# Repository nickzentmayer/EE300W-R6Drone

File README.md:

# EE300W-R6Drone
Repository containing all code and CAD design files for EE300W project SP26

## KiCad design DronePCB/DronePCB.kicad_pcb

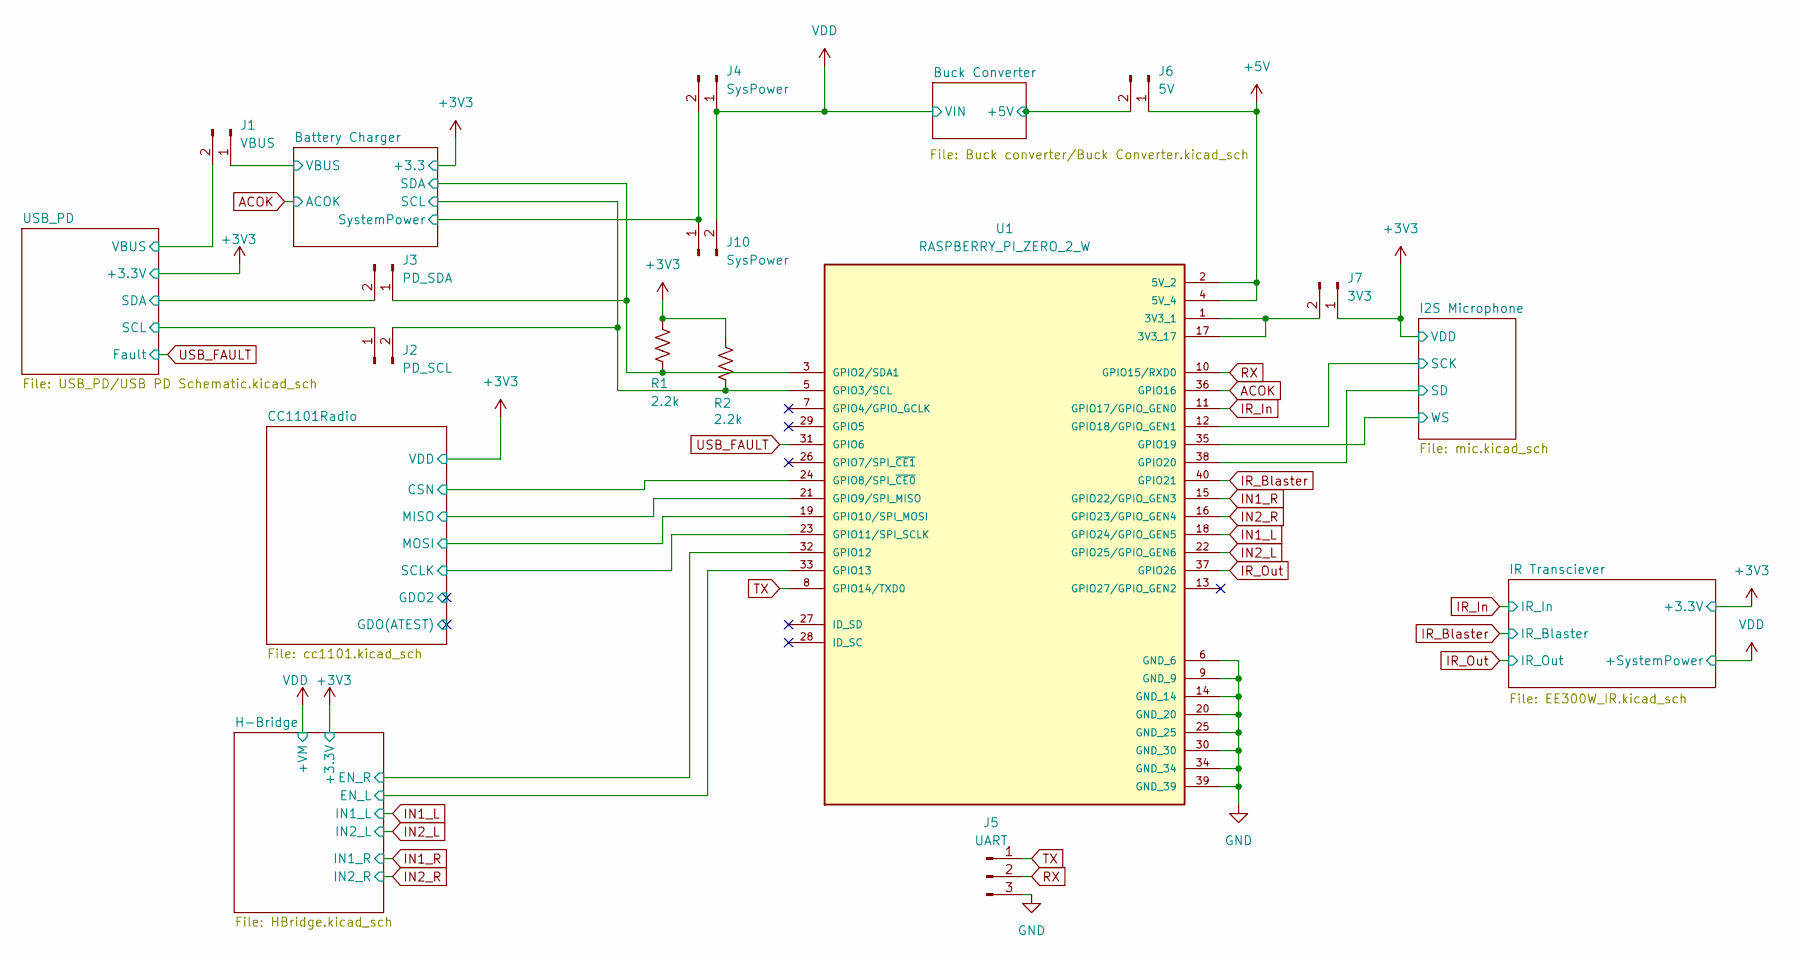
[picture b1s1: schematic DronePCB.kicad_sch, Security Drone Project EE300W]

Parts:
J1: VBUS; PinHeader_1x02_P2.54mm_Vertical
J2: PD_SCL; PinHeader_1x02_P2.54mm_Vertical
J3: PD_SDA; PinHeader_1x02_P2.54mm_Vertical
J4, J10: SysPower; PinHeader_1x02_P2.54mm_Vertical
J5: UART; PinHeader_1x03_P2.54mm_Vertical
J6: 5V; PinHeader_1x02_P2.54mm_Vertical
J7: 3V3; PinHeader_1x02_P2.54mm_Vertical
R1, R2: 2.2k; R_0603_1608Metric
U1: RASPBERRY_PI_ZERO_2_W; MODULE_RASPBERRY_PI_ZERO_2_W; PARTREV April 2024

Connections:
+3V3: J7.1, R1.1, R2.1; also elsewhere on the board
+5V: J6.1, U1.2 (5V_2), U1.4 (5V_4)
/Battery Charger/SCL: J2.2, R2.2, U1.5 (GPIO3/SCL); also elsewhere on the board
/Battery Charger/SDA: J3.1, R1.2, U1.3 (GPIO2/SDA1); also elsewhere on the board
/Battery Charger/SystemPower: J4.2, J10.1; also elsewhere on the board
/Battery Charger/VBUS: J1.1; also elsewhere on the board
/Buck Converter/+5V: J6.2; also elsewhere on the board
/CC1101Radio/CSN: U1.24 (GPIO8/SPI_~CE0); also elsewhere on the board
/CC1101Radio/MISO: U1.21 (GPIO9/SPI_MISO); also elsewhere on the board
/CC1101Radio/MOSI: U1.19 (GPIO10/SPI_MOSI); also elsewhere on the board
/CC1101Radio/SCLK: U1.23 (GPIO11/SPI_SCLK); also elsewhere on the board
/H-Bridge/EN_L: U1.33 (GPIO13); also elsewhere on the board
/H-Bridge/EN_R: U1.32 (GPIO12); also elsewhere on the board
/I2S Microphone/SCK: U1.12 (GPIO18/GPIO_GEN1); also elsewhere on the board
/I2S Microphone/SD: U1.38 (GPIO20); also elsewhere on the board
/I2S Microphone/WS: U1.35 (GPIO19); also elsewhere on the board
/USB_PD/SCL: J2.1; also elsewhere on the board
/USB_PD/SDA: J3.2; also elsewhere on the board
/USB_PD/VBUS: J1.2; also elsewhere on the board
ACOK: U1.36 (GPIO16); also elsewhere on the board
GND: J5.3, U1.6 (GND_6), U1.9 (GND_9), U1.14 (GND_14), U1.20 (GND_20), U1.25 (GND_25), U1.30 (GND_30), U1.34 (GND_34), U1.39 (GND_39); also elsewhere on the board
IN1_L: U1.18 (GPIO24/GPIO_GEN5); also elsewhere on the board
IN1_R: U1.15 (GPIO22/GPIO_GEN3); also elsewhere on the board
IN2_L: U1.22 (GPIO25/GPIO_GEN6); also elsewhere on the board
IN2_R: U1.16 (GPIO23/GPIO_GEN4); also elsewhere on the board
IR_Blaster: U1.40 (GPIO21); also elsewhere on the board
IR_In: U1.11 (GPIO17/GPIO_GEN0); also elsewhere on the board
IR_Out: U1.37 (GPIO26); also elsewhere on the board
unnamed: J7.2, U1.1 (3V3_1), U1.17 (3V3_17)
RX: J5.2, U1.10 (GPIO15/RXD0)
TX: J5.1, U1.8 (GPIO14/TXD0)
USB_FAULT: U1.31 (GPIO6); also elsewhere on the board
VDD: J4.1, J10.2; also elsewhere on the board

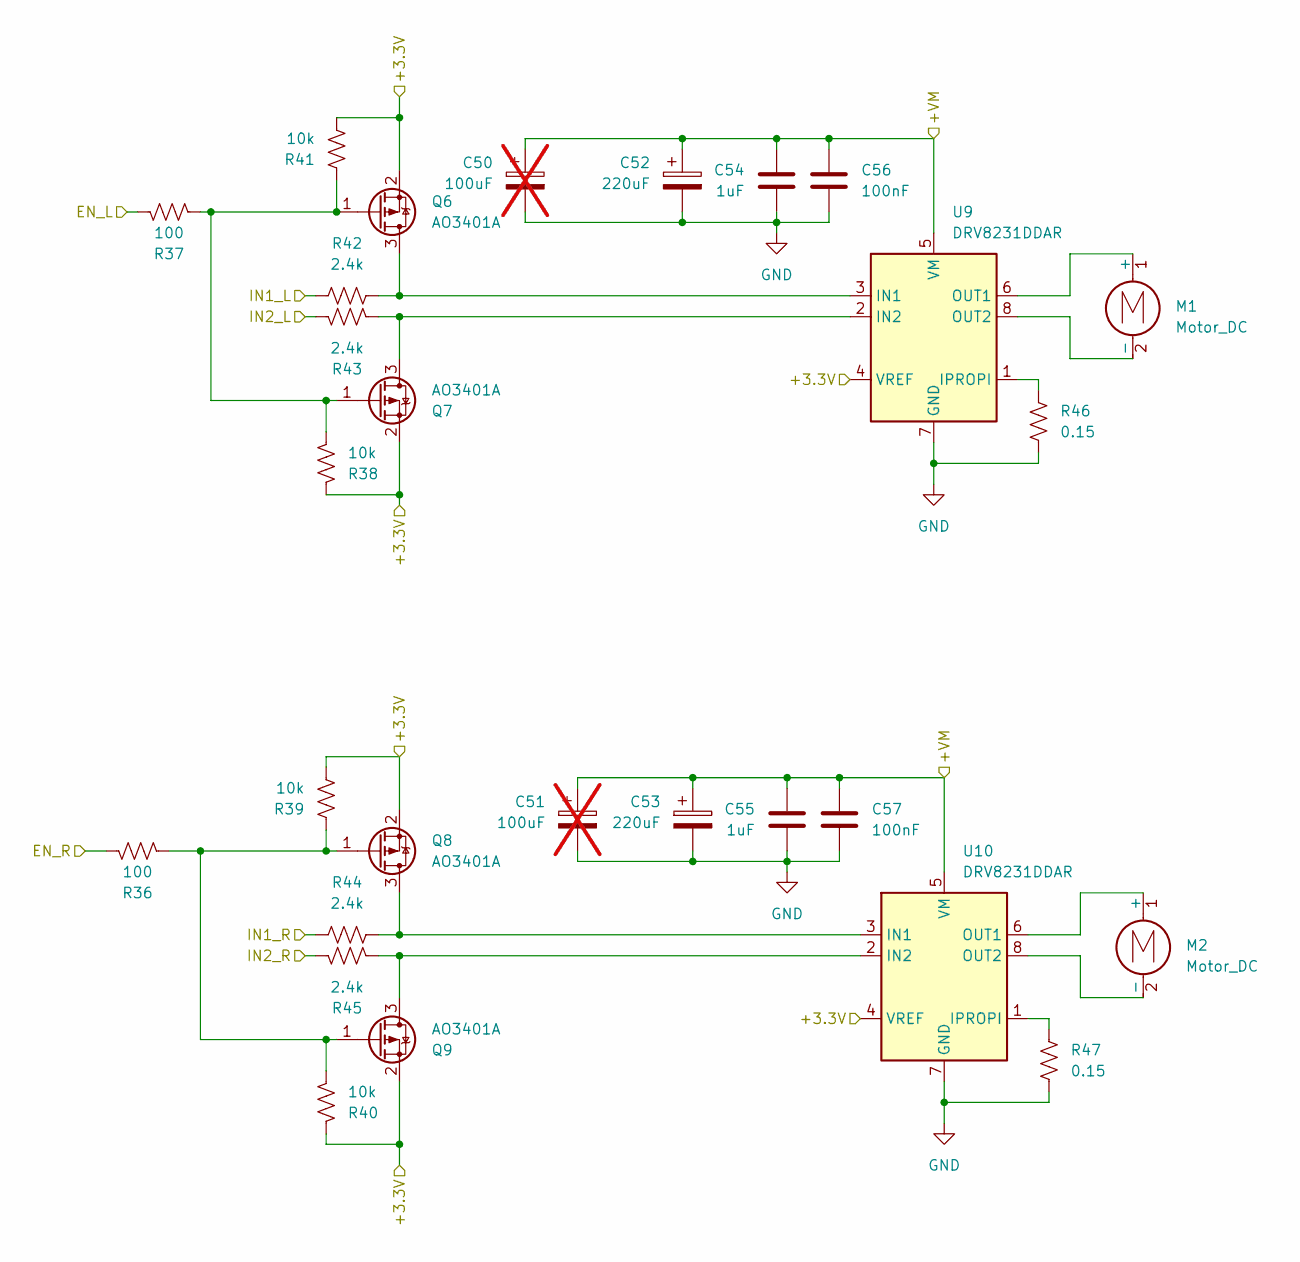
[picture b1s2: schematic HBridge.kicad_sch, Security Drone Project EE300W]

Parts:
C50, C51: 100uF; CP_Radial_D6.3mm_P2.50mm; not fitted
C52, C53: 220uF; CP_Radial_D6.3mm_P2.50mm
C54, C55: 1uF; C_0603_1608Metric
C56, C57: 100nF; C_0603_1608Metric
M1, M2: Motor_DC; SolderWire-0.5sqmm_1x02_P4.6mm_D0.9mm_OD2.1mm_Relief
Q6, Q7, Q8, Q9: AO3401A; SOT-23
R36, R37: 100; R_0603_1608Metric
R38, R39, R40, R41: 10k; R_0603_1608Metric
R42, R43, R44, R45: 2.4k; R_0603_1608Metric
R46, R47: 0.15; R_0603_1608Metric
U9, U10: DRV8231DDAR; HSOP-8-1EP_3.9x4.9mm_P1.27mm_EP2.41x3.1mm_ThermalVias

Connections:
+3V3: Q6.2 (S), Q7.2 (S), Q8.2 (S), Q9.2 (S), R38.1, R39.2, R40.1, R41.2, U9.4 (VREF), U10.4 (VREF); also elsewhere on the board
/H-Bridge/EN_L: R37.1; also elsewhere on the board
/H-Bridge/EN_R: R36.1; also elsewhere on the board
GND: C50.2, C51.2, C52.2, C53.2, C54.2, C55.2, C56.2, C57.2, R46.2, R47.2, U9.7 (GND), U9.9 (GND), U10.7 (GND), U10.9 (GND); also elsewhere on the board
IN1_L: R42.1; also elsewhere on the board
IN1_R: R44.1; also elsewhere on the board
IN2_L: R43.1; also elsewhere on the board
IN2_R: R45.1; also elsewhere on the board
unnamed: M1.1 (+), U9.6 (OUT1)
unnamed: M1.2 (-), U9.8 (OUT2)
unnamed: M2.1 (+), U10.6 (OUT1)
unnamed: M2.2 (-), U10.8 (OUT2)
unnamed: Q6.3 (D), R42.2, U9.3 (IN1)
unnamed: Q6.1 (G), Q7.1 (G), R37.2, R38.2, R41.1
unnamed: Q7.3 (D), R43.2, U9.2 (IN2)
unnamed: Q8.3 (D), R44.2, U10.3 (IN1)
unnamed: Q8.1 (G), Q9.1 (G), R36.2, R39.1, R40.2
unnamed: Q9.3 (D), R45.2, U10.2 (IN2)
unnamed: R46.1, U9.1 (IPROPI)
unnamed: R47.1, U10.1 (IPROPI)
VDD: C50.1, C51.1, C52.1, C53.1, C54.1, C55.1, C56.1, C57.1, U9.5 (VM), U10.5 (VM); also elsewhere on the board

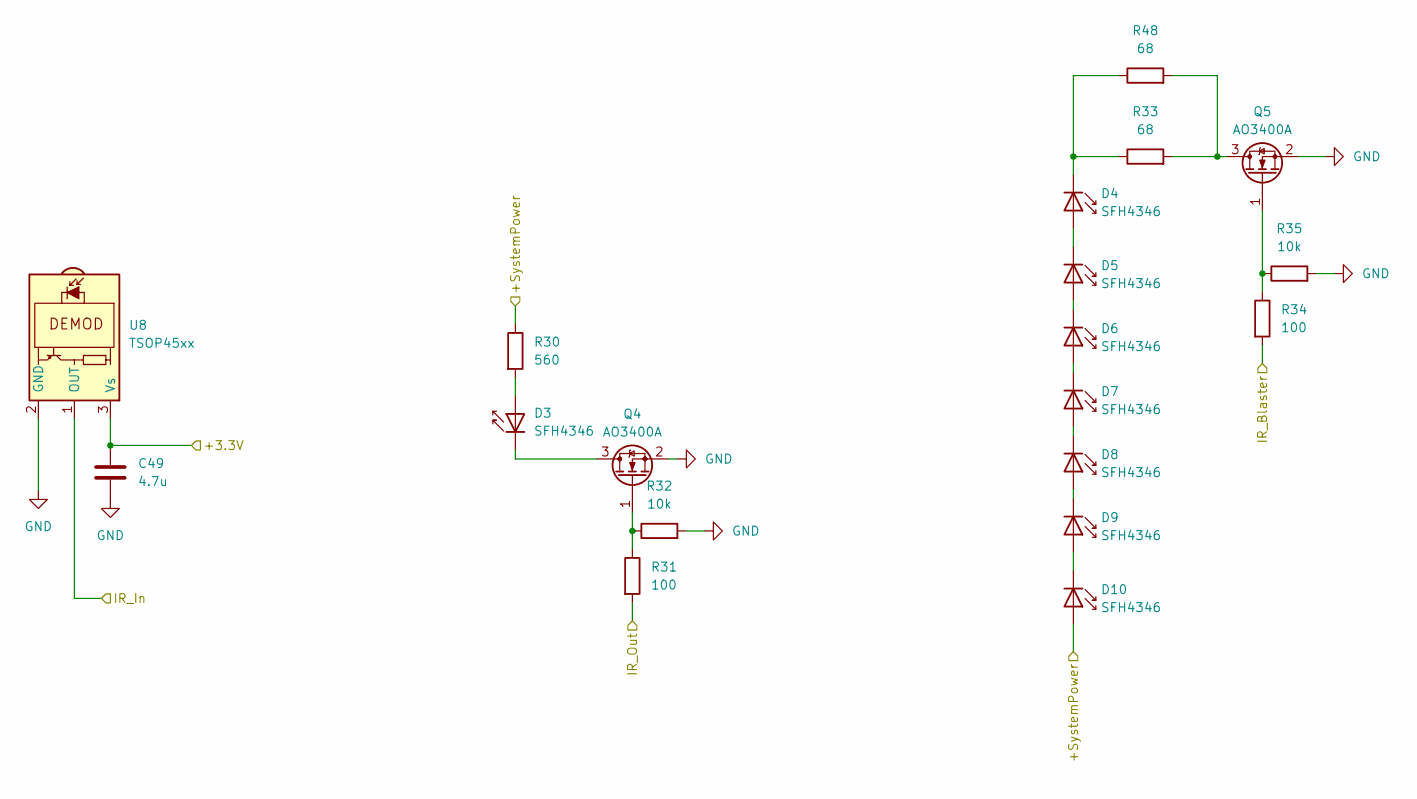
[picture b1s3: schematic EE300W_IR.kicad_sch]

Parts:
C49: 4.7u; C_0603_1608Metric
D3, D4, D5, D6, D7, D8, D9, D10: SFH4346; LED_D5.0mm_IRGrey
Q4, Q5: AO3400A; SOT-23
R30: 560; R_0603_1608Metric
R31, R34: 100; R_0603_1608Metric
R32, R35: 10k; R_0603_1608Metric
R33, R48: 68; R_1206_3216Metric
U8: TSOP45xx; Vishay_MOLD-3Pin

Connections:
+3V3: C49.1, U8.3 (Vs); also elsewhere on the board
GND: C49.2, Q4.2 (S), Q5.2 (S), R32.2, R35.2, U8.2 (GND); also elsewhere on the board
IR_Blaster: R34.2; also elsewhere on the board
IR_In: U8.1 (OUT); also elsewhere on the board
IR_Out: R31.2; also elsewhere on the board
unnamed: D3.2 (A), R30.2
unnamed: D3.1 (K), Q4.3 (D)
unnamed: D4.2 (A), D5.1 (K)
unnamed: D4.1 (K), R33.1, R48.1
unnamed: D5.2 (A), D6.1 (K)
unnamed: D6.2 (A), D7.1 (K)
unnamed: D7.2 (A), D8.1 (K)
unnamed: D8.2 (A), D9.1 (K)
unnamed: D9.2 (A), D10.1 (K)
unnamed: Q4.1 (G), R31.1, R32.1
unnamed: Q5.3 (D), R33.2, R48.2
unnamed: Q5.1 (G), R34.1, R35.1
VDD: D10.2 (A), R30.1; also elsewhere on the board

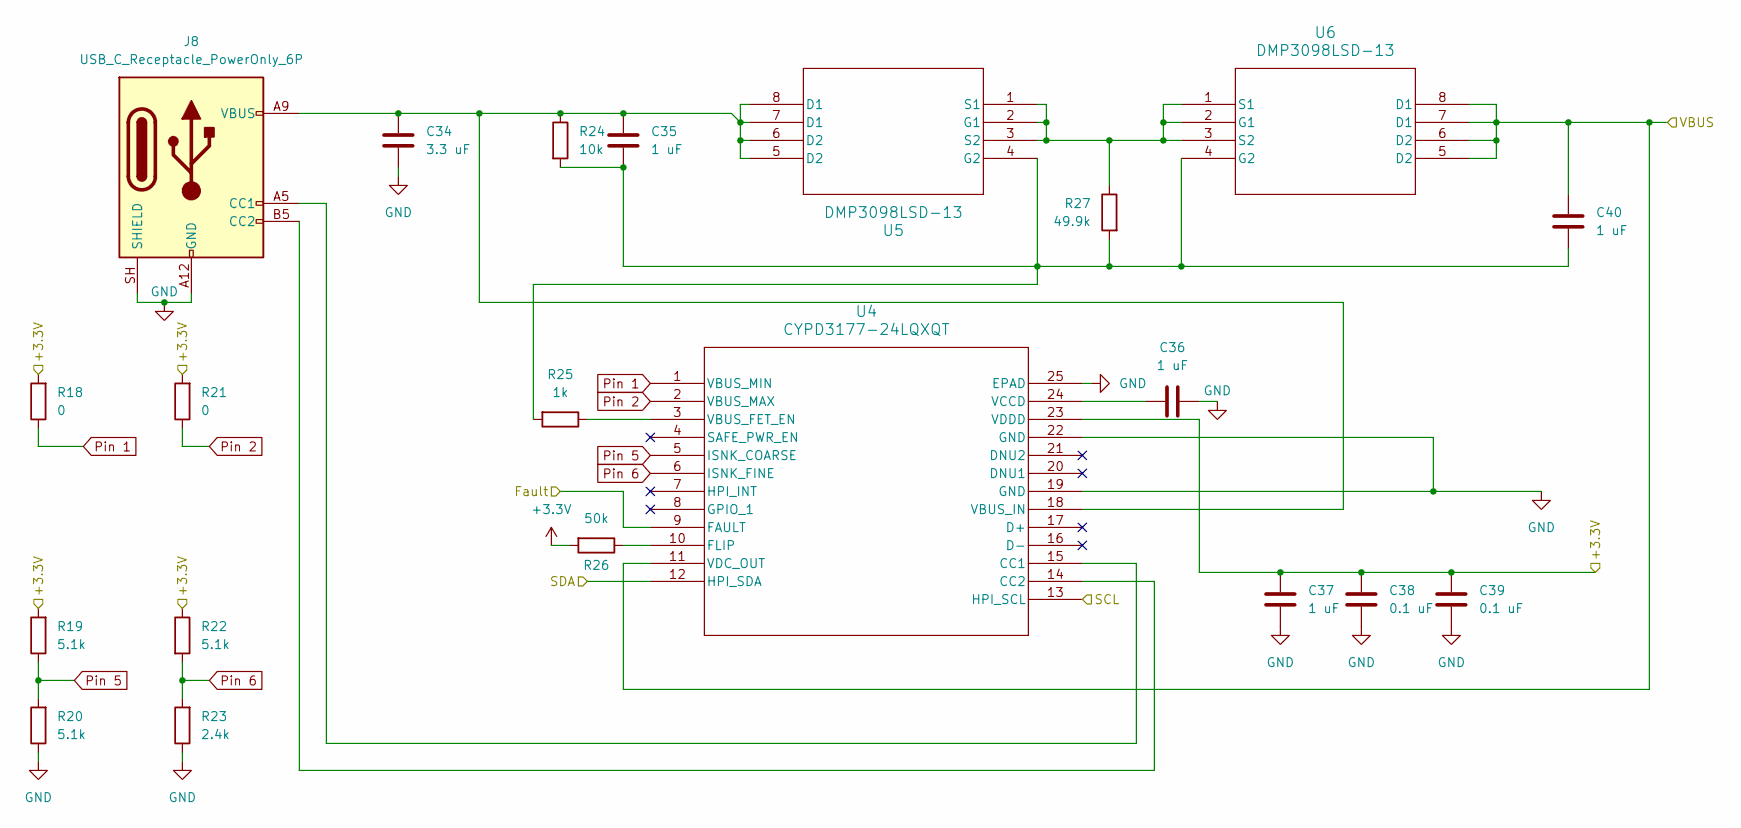
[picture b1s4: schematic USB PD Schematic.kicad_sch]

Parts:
C34: 3.3 uF; C_0603_1608Metric
C35, C36, C37, C40: 1 uF; C_0603_1608Metric
C38, C39: 0.1 uF; C_0603_1608Metric
J8: USB_C_Receptacle_PowerOnly_6P; USB_C_Receptacle_GCT_USB4125-xx-x_6P_TopMnt_Horizontal
R18, R21: 0; R_0603_1608Metric
R19, R20, R22: 5.1k; R_0603_1608Metric
R23: 2.4k; R_0603_1608Metric
R24: 10k; R_0603_1608Metric
R25: 1k; R_0603_1608Metric
R26: 50k; R_0603_1608Metric
R27: 49.9k; R_0603_1608Metric
U4: CYPD3177-24LQXQT; QFN24_CYPD3177-24LQXQT_INF
U5, U6: DMP3098LSD-13; SOP_DMP3098LSD-13_DIO

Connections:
+3V3: C37.1, C38.1, C39.1, R18.2, R19.2, R21.2, R22.1, R26.2, U4.23 (VDDD); also elsewhere on the board
/USB_PD/SCL: U4.13 (HPI_SCL); also elsewhere on the board
/USB_PD/SDA: U4.12 (HPI_SDA); also elsewhere on the board
/USB_PD/VBUS: C40.1, U4.11 (VDC_OUT), U6.5 (D2), U6.6 (D2), U6.7 (D1), U6.8 (D1); also elsewhere on the board
GND: C34.2, C36.1, C37.2, C38.2, C39.2, J8.A12 (GND), J8.B12 (GND), J8.SH (SHIELD), R20.1, R23.1, U4.19 (GND), U4.22 (GND), U4.25 (EPAD); also elsewhere on the board
unnamed: J8.A5 (CC1), U4.15 (CC1)
unnamed: J8.B5 (CC2), U4.14 (CC2)
unnamed: R26.1, U4.10 (FLIP)
unnamed: R25.1, U4.3 (VBUS_FET_EN)
unnamed: C34.1, C35.1, J8.A9 (VBUS), J8.B9 (VBUS), R24.1, U4.18 (VBUS_IN), U5.5 (D2), U5.6 (D2), U5.7 (D1), U5.8 (D1)
unnamed: C36.2, U4.24 (VCCD)
unnamed: R27.1, U5.1 (S1), U5.2 (G1), U5.3 (S2), U6.1 (S1), U6.2 (G1), U6.3 (S2)
unnamed: C35.2, C40.2, R24.2, R25.2, R27.2, U5.4 (G2), U6.4 (G2)
Pin 1: R18.1, U4.1 (VBUS_MIN)
Pin 2: R21.1, U4.2 (VBUS_MAX)
Pin 5: R19.1, R20.2, U4.5 (ISNK_COARSE)
Pin 6: R22.2, R23.2, U4.6 (ISNK_FINE)
USB_FAULT: U4.9 (FAULT); also elsewhere on the board

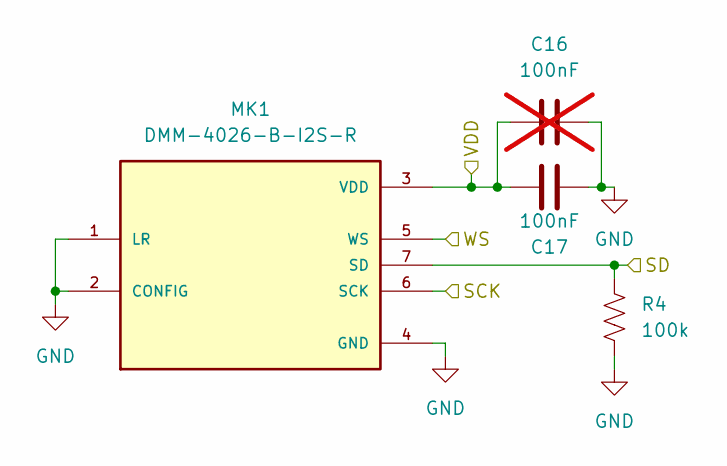
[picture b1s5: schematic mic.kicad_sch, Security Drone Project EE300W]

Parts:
C16: 100nF; C_0603_1608Metric; not fitted
C17: 100nF; C_0603_1608Metric
MK1: DMM-4026-B-I2S-R; MIC_DMM-4026-B-I2S-R; PARTREV A
R4: 100k; R_0603_1608Metric

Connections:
+3V3: C16.1, C17.1, MK1.3 (VDD); also elsewhere on the board
/I2S Microphone/SCK: MK1.6 (SCK); also elsewhere on the board
/I2S Microphone/SD: MK1.7 (SD), R4.1; also elsewhere on the board
/I2S Microphone/WS: MK1.5 (WS); also elsewhere on the board
GND: C16.2, C17.2, MK1.1 (LR), MK1.2 (CONFIG), MK1.4 (GND), R4.2; also elsewhere on the board

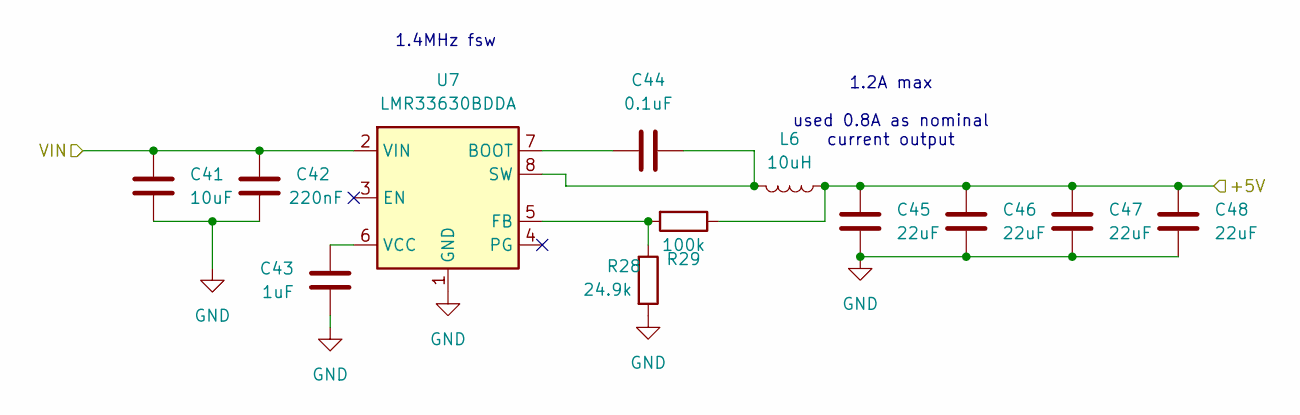
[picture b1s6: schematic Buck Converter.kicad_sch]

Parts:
C41: 10uF; C_1206_3216Metric
C42: 220nF; C_0603_1608Metric
C43: 1uF; C_0603_1608Metric
C44: 0.1uF; C_0603_1608Metric
C45, C46, C47, C48: 22uF; C_0603_1608Metric
L6: 10uH; L_Taiyo-Yuden_NR-40xx
R28: 24.9k; R_0603_1608Metric
R29: 100k; R_0603_1608Metric
U7: LMR33630BDDA; Texas_HSOP-8-1EP_3.9x4.9mm_P1.27mm_ThermalVias

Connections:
/Buck Converter/+5V: C45.1, C46.1, C47.1, C48.1, L6.1, R29.1; also elsewhere on the board
GND: C41.2, C42.2, C43.2, C45.2, C46.2, C47.2, C48.2, R28.2, U7.1 (GND), U7.9 (GND); also elsewhere on the board
unnamed: C44.2, U7.7 (BOOT)
unnamed: R28.1, R29.2, U7.5 (FB)
unnamed: C44.1, L6.2, U7.8 (SW)
unnamed: C43.1, U7.6 (VCC)
VDD: C41.1, C42.1, U7.2 (VIN); also elsewhere on the board

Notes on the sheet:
1.4MHz fsw
1.2A max used 0.8A as nominal current output

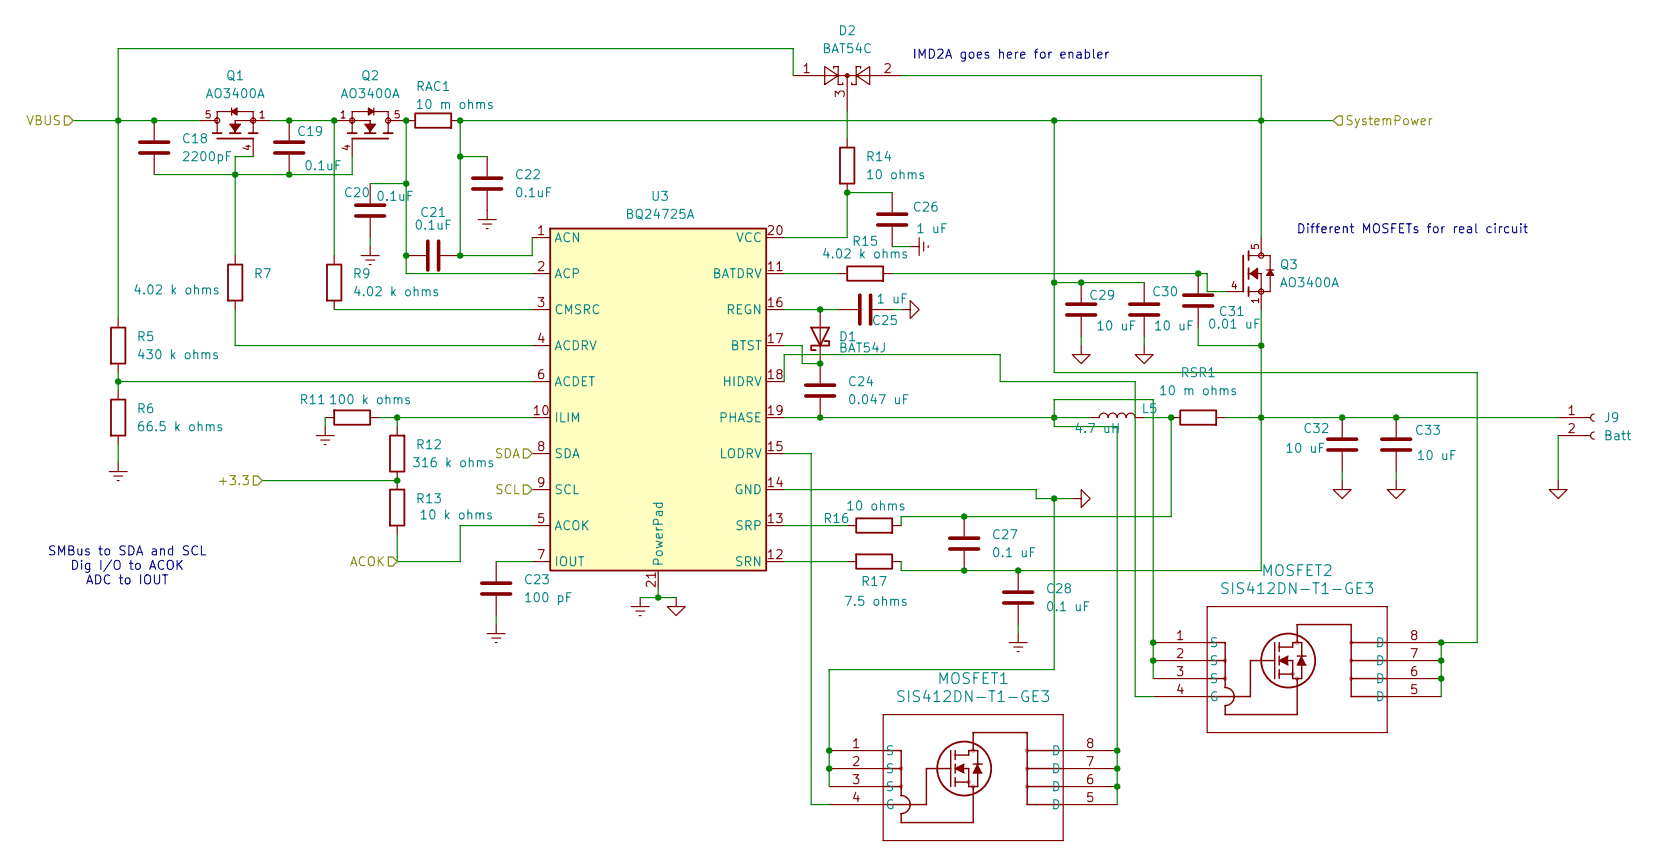
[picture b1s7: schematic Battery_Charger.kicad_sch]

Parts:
C18: 2200pF; C_1210_3225Metric
C19, C20, C21, C22: 0.1uF; C_0603_1608Metric
C23: 100 pF; C_0603_1608Metric
C24: 0.047 uF; C_0603_1608Metric
C25, C26: 1 uF; C_0603_1608Metric
C27, C28: 0.1 uF; C_0603_1608Metric
C29, C30, C32, C33: 10 uF; C_1206_3216Metric
C31: 0.01 uF; C_0603_1608Metric
D1: BAT54J; D_SOD-323F
D2: BAT54C; SOT-23
J9: Batt; SolderWire-0.25sqmm_1x02_P4.2mm_D0.65mm_OD1.7mm_Relief
L5: 4.7 uH; L_Vishay_IHLP-2525
MOSFET1, MOSFET2: SIS412DN-T1-GE3; Vishay_PowerPAK_1212-8_Single
Q1: AO3400A; SO-8_3.9x4.9mm_P1.27mm; PARTREV 6; DigiKey_Part_Number FDS6680ACT-ND
Q2, Q3: AO3400A; SO-8_3.9x4.9mm_P1.27mm
R5: 430 k ohms; R_0603_1608Metric
R6: 66.5 k ohms; R_0603_1608Metric
R7, R9, R15: 4.02 k ohms; R_0603_1608Metric
R11: 100 k ohms; R_0603_1608Metric
R12: 316 k ohms; R_0603_1608Metric
R13: 10 k ohms; R_0603_1608Metric
R14, R16: 10 ohms; R_0603_1608Metric
R17: 7.5 ohms; R_0603_1608Metric
RAC1: 10 m ohms; R_0603_1608Metric
RSR1: 10 m ohms; R_0603_1608Metric
U3: BQ24725A; QFN50P350X350X100-21N

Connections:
+3V3: R12.1, R13.1; also elsewhere on the board
/Battery Charger/SCL: U3.9 (SCL); also elsewhere on the board
/Battery Charger/SDA: U3.8 (SDA); also elsewhere on the board
/Battery Charger/SystemPower: C21.1, C22.1, C29.1, C30.1, D2.2, MOSFET2.5 (D), MOSFET2.6 (D), MOSFET2.7 (D), MOSFET2.8 (D), Q3.5, Q3.6, Q3.7, Q3.8, RAC1.2, U3.1 (ACN); also elsewhere on the board
/Battery Charger/VBUS: C18.1, D2.1, Q1.5, Q1.6, Q1.7, Q1.8, R5.1; also elsewhere on the board
ACOK: R13.2, U3.5 (ACOK); also elsewhere on the board
GND: C20.2, C22.2, C23.2, C25.1, C26.2, C28.2, C29.2, C30.2, C32.2, C33.2, J9.2, MOSFET1.1 (S), MOSFET1.2 (S), MOSFET1.3 (S), R6.2, R11.2, U3.14 (GND), U3.21 (PowerPad); also elsewhere on the board
unnamed: C18.2, C19.2, Q1.4, Q2.4, R7.1
unnamed: C19.1, Q1.1, Q1.2, Q1.3, Q2.1, Q2.2, Q2.3, R9.1
unnamed: C27.1, L5.2, R16.2, RSR1.1
unnamed: C31.1, Q3.4, R15.2
unnamed: C25.2, D1.2 (A), U3.16 (REGN)
unnamed: C24.1, D1.1 (K), U3.17 (BTST)
unnamed: D2.3, R14.1
unnamed: C27.2, C28.1, C31.2, C32.1, C33.1, J9.1, Q3.1, Q3.2, Q3.3, R17.1, RSR1.2
unnamed: MOSFET1.4 (G), U3.15 (LODRV)
unnamed: MOSFET2.4 (G), U3.18 (HIDRV)
unnamed: R5.2, R6.1, U3.6 (ACDET)
unnamed: R7.2, U3.4 (ACDRV)
unnamed: C20.1, C21.2, Q2.5, Q2.6, Q2.7, Q2.8, RAC1.1, U3.2 (ACP)
unnamed: R15.1, U3.11 (BATDRV)
unnamed: R9.2, U3.3 (CMSRC)
unnamed: R11.1, R12.2, U3.10 (ILIM)
unnamed: C23.1, U3.7 (IOUT)
unnamed: C24.2, L5.1, MOSFET1.5 (D), MOSFET1.6 (D), MOSFET1.7 (D), MOSFET1.8 (D), MOSFET2.1 (S), MOSFET2.2 (S), MOSFET2.3 (S), U3.19 (PHASE)
unnamed: R17.2, U3.12 (SRN)
unnamed: R16.1, U3.13 (SRP)
unnamed: C26.1, R14.2, U3.20 (VCC)

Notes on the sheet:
SMBus to SDA and SCL Dig I/O to ACOK ADC to IOUT
Different MOSFETs for real circuit
IMD2A goes here for enabler

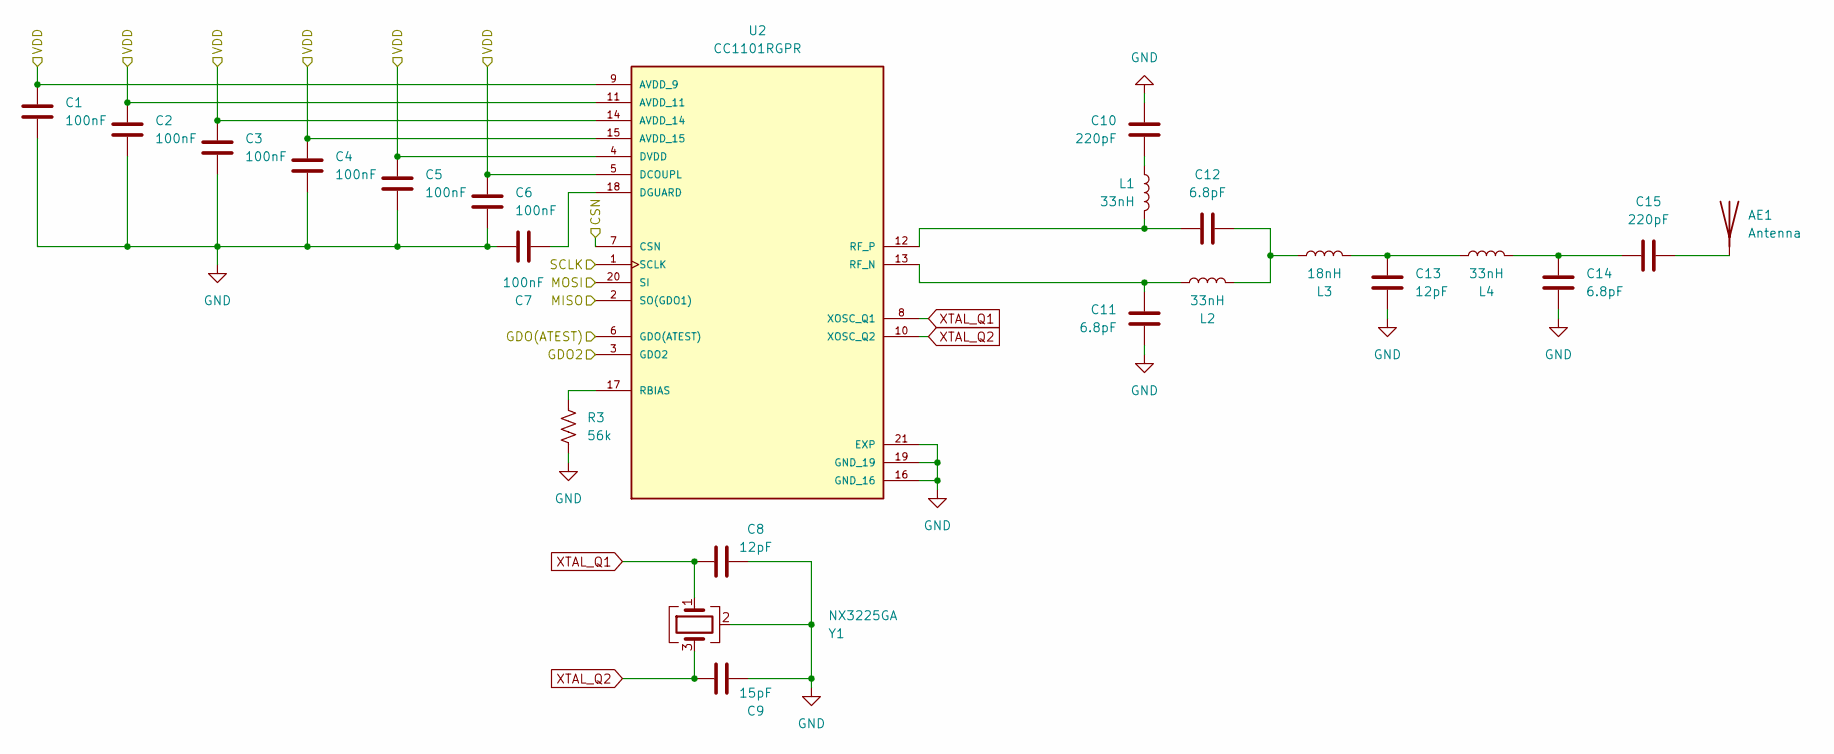
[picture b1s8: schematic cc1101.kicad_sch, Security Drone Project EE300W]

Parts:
AE1: Antenna; ANT1204F002R0315A
C1, C2, C3, C4, C5, C6, C7: 100nF; C_0603_1608Metric
C8: 12pF; C_0603_1608Metric
C9: 15pF; C_0603_1608Metric
C10, C15: 220pF; C_0402_1005Metric
C11, C12, C14: 6.8pF; C_0402_1005Metric
C13: 12pF; C_0402_1005Metric
L1, L2, L4: 33nH; L_0402_1005Metric
L3: 18nH; L_0402_1005Metric
R3: 56k; R_0603_1608Metric
U2: CC1101RGPR; QFN50P400X400X100-21N; PARTREV 6-May-2020
Y1: NX3225GA; Crystal_SMD_3225-4Pin_3.2x2.5mm

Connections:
+3V3: C1.1, C2.1, C3.1, C4.1, C5.1, C6.1, U2.4 (DVDD), U2.5 (DCOUPL), U2.9 (AVDD_9), U2.11 (AVDD_11), U2.14 (AVDD_14), U2.15 (AVDD_15); also elsewhere on the board
/CC1101Radio/CSN: U2.7 (CSN); also elsewhere on the board
/CC1101Radio/GDO2: U2.3 (GDO2)
/CC1101Radio/GDO(ATEST): U2.6 (GDO(ATEST))
/CC1101Radio/MISO: U2.2 (SO(GDO1)); also elsewhere on the board
/CC1101Radio/MOSI: U2.20 (SI); also elsewhere on the board
/CC1101Radio/SCLK: U2.1 (SCLK); also elsewhere on the board
GND: C1.2, C2.2, C3.2, C4.2, C5.2, C6.2, C7.2, C8.2, C9.2, C10.2, C11.1, C13.2, C14.2, R3.2, U2.16 (GND_16), U2.19 (GND_19), U2.21 (EXP), Y1.2 (G), Y1.4 (G); also elsewhere on the board
unnamed 30: AE1.1, C15.2; also elsewhere on the board
unnamed: C10.1, L1.2
unnamed: C12.1, L2.1, L3.2
unnamed: C13.1, L3.1, L4.2
unnamed: C14.1, C15.1, L4.1
unnamed: C7.1, U2.18 (DGUARD)
unnamed: R3.1, U2.17 (RBIAS)
unnamed: C11.2, L2.2, U2.13 (RF_N)
unnamed: C12.2, L1.1, U2.12 (RF_P)
XTAL_Q1: C8.1, U2.8 (XOSC_Q1), Y1.1
XTAL_Q2: C9.1, U2.10 (XOSC_Q2), Y1.3

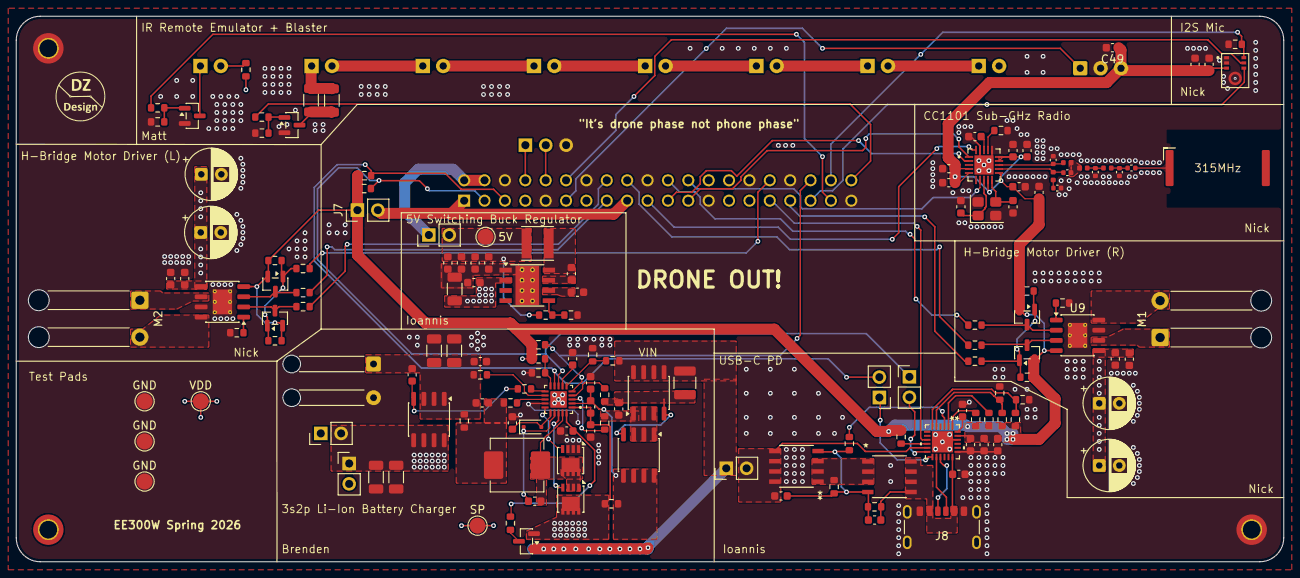
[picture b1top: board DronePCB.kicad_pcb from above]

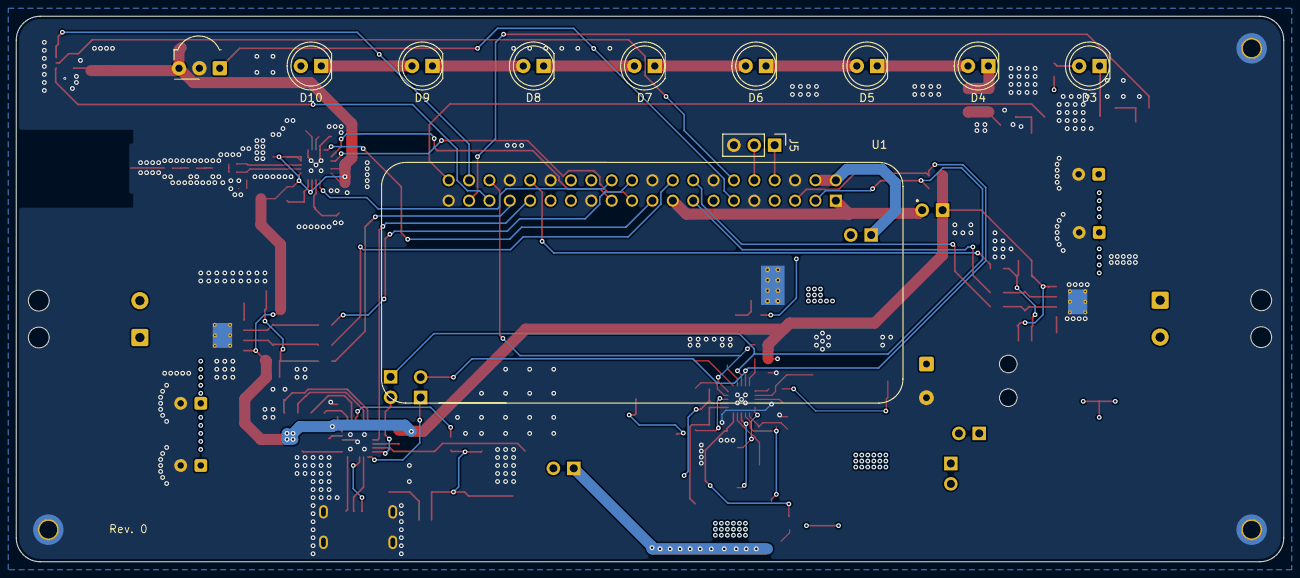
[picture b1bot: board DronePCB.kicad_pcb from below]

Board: 4 copper layers, 158.0 x 68.0 mm, 163 parts (10 on the bottom side), 105 nets.

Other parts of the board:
5V: TestPoint_Pad_D2.0mm
315MHz: Antenna; ANT1204F002R0315A
GND: TestPoint_Pad_D2.0mm
GND#2, GND#3: TestPoint_Pad_D2.0mm
SP: TestPoint_Pad_D2.0mm
VDD: TestPoint_Pad_D2.0mm

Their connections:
GND: GND.1, GND#2.1, GND#3.1; also elsewhere on the board
unnamed 30: 315MHz.1 (A_1); also elsewhere on the board
VDD: VDD.1; also elsewhere on the board

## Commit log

2026-03-13 Initial commit - Started CC1101 Schematic
2026-03-14 Completed CC1101 Radio Schematic
2026-03-14 Finished CC1101 Schematic
2026-03-15 Finished and wired up CC1101 and Microphone circuits
2026-03-17 Added mic schematic, extra DNP decouple Cap, fixed 3v3 wiring
2026-03-19 ShoppingList
    Item list for Battery Charger
2026-03-19 Rename ShoppingList to ShoppingList.md
2026-03-20 Add files via upload
    IR Schematics (Receiver, Universal Remote, Night Vision)
2026-03-20 Rename DronePCB/Battery_Charger_Circuit.pdf to DronePCB/BatteryCharger/Battery_Charger_Circuit.pdf
2026-03-20 Incorperated IR Ciruit into main schematic
2026-03-20 added motor driver
2026-03-23 Create H bridge
2026-03-26 Create USB-PD
2026-03-26 Power_delivery_Sch
2026-03-26 Create Notes
2026-03-26 Fixed a connection in battery circuit and updated project to KiCAD 10.0.0
2026-03-26 Update Notes
2026-03-26 Rename USB PD.kicad_sch to USB PD Schematic
2026-03-27 Integrated and cleaned up almost all circuits into main schematic | added jumpers where nessecary
2026-03-27 Added IR circuit to main schematic | fixed RPi header gnd
2026-03-30 Completed H-Bridge Circuit | Finished Schematic | Working on pcb design
2026-03-30 finished H bridge pcb design
2026-03-31 Finished CC1101 Radio Circuit
2026-03-31 removed .DS-Store
2026-04-02 All circuits complete
2026-04-03 Rough board placement complete
2026-04-04 Changed Resistor on IR Blaster | Finished Running DRC on PCB
2026-04-04 Added finishing details to PCB
2026-04-07 Finalized Drone PCB
2026-04-07 Finalized and Exported PCB as STEP file
2026-04-10 slight pcb tweaks
2026-04-11 Create Ioannis' Parts
2026-04-11 Update Ioannis' Parts
2026-04-23 Demo Code Working
